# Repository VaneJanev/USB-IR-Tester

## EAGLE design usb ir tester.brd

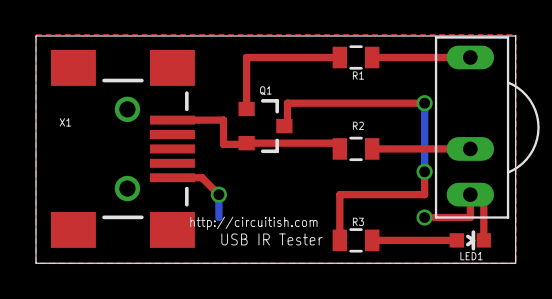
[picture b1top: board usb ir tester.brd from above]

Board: 2 copper layers, 26.7 x 12.6 mm, 7 parts (0 on the bottom side), 7 nets.

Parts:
LED1: LED-0603
Q1: BC558; SOT23-3
R1, R3: 1K; 0805
R2: 33R; 0805
U$1: TSOP1738; TSOP17XX
X1: USB Mini; USB-MINIB-NOSTOP

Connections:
GND: LED1.C, U$1.GND, X1.GND
unnamed: R1.2, U$1.OUT
unnamed: Q1.3, R3.1
unnamed: Q1.1, R1.1
unnamed: LED1.A, R3.2
unnamed: R2.2, U$1.V+
VCC: Q1.2, R2.1, X1.VBUS

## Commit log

2015-06-03 :space_invader: Added .gitattributes
2015-06-03 USB IR Tester
    Eagle Files

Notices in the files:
parts and their libraries:
SparkFun-Connectors: Licensing: CC v3.0 Share-Alike You are welcome to use this library for commercial purposes.
